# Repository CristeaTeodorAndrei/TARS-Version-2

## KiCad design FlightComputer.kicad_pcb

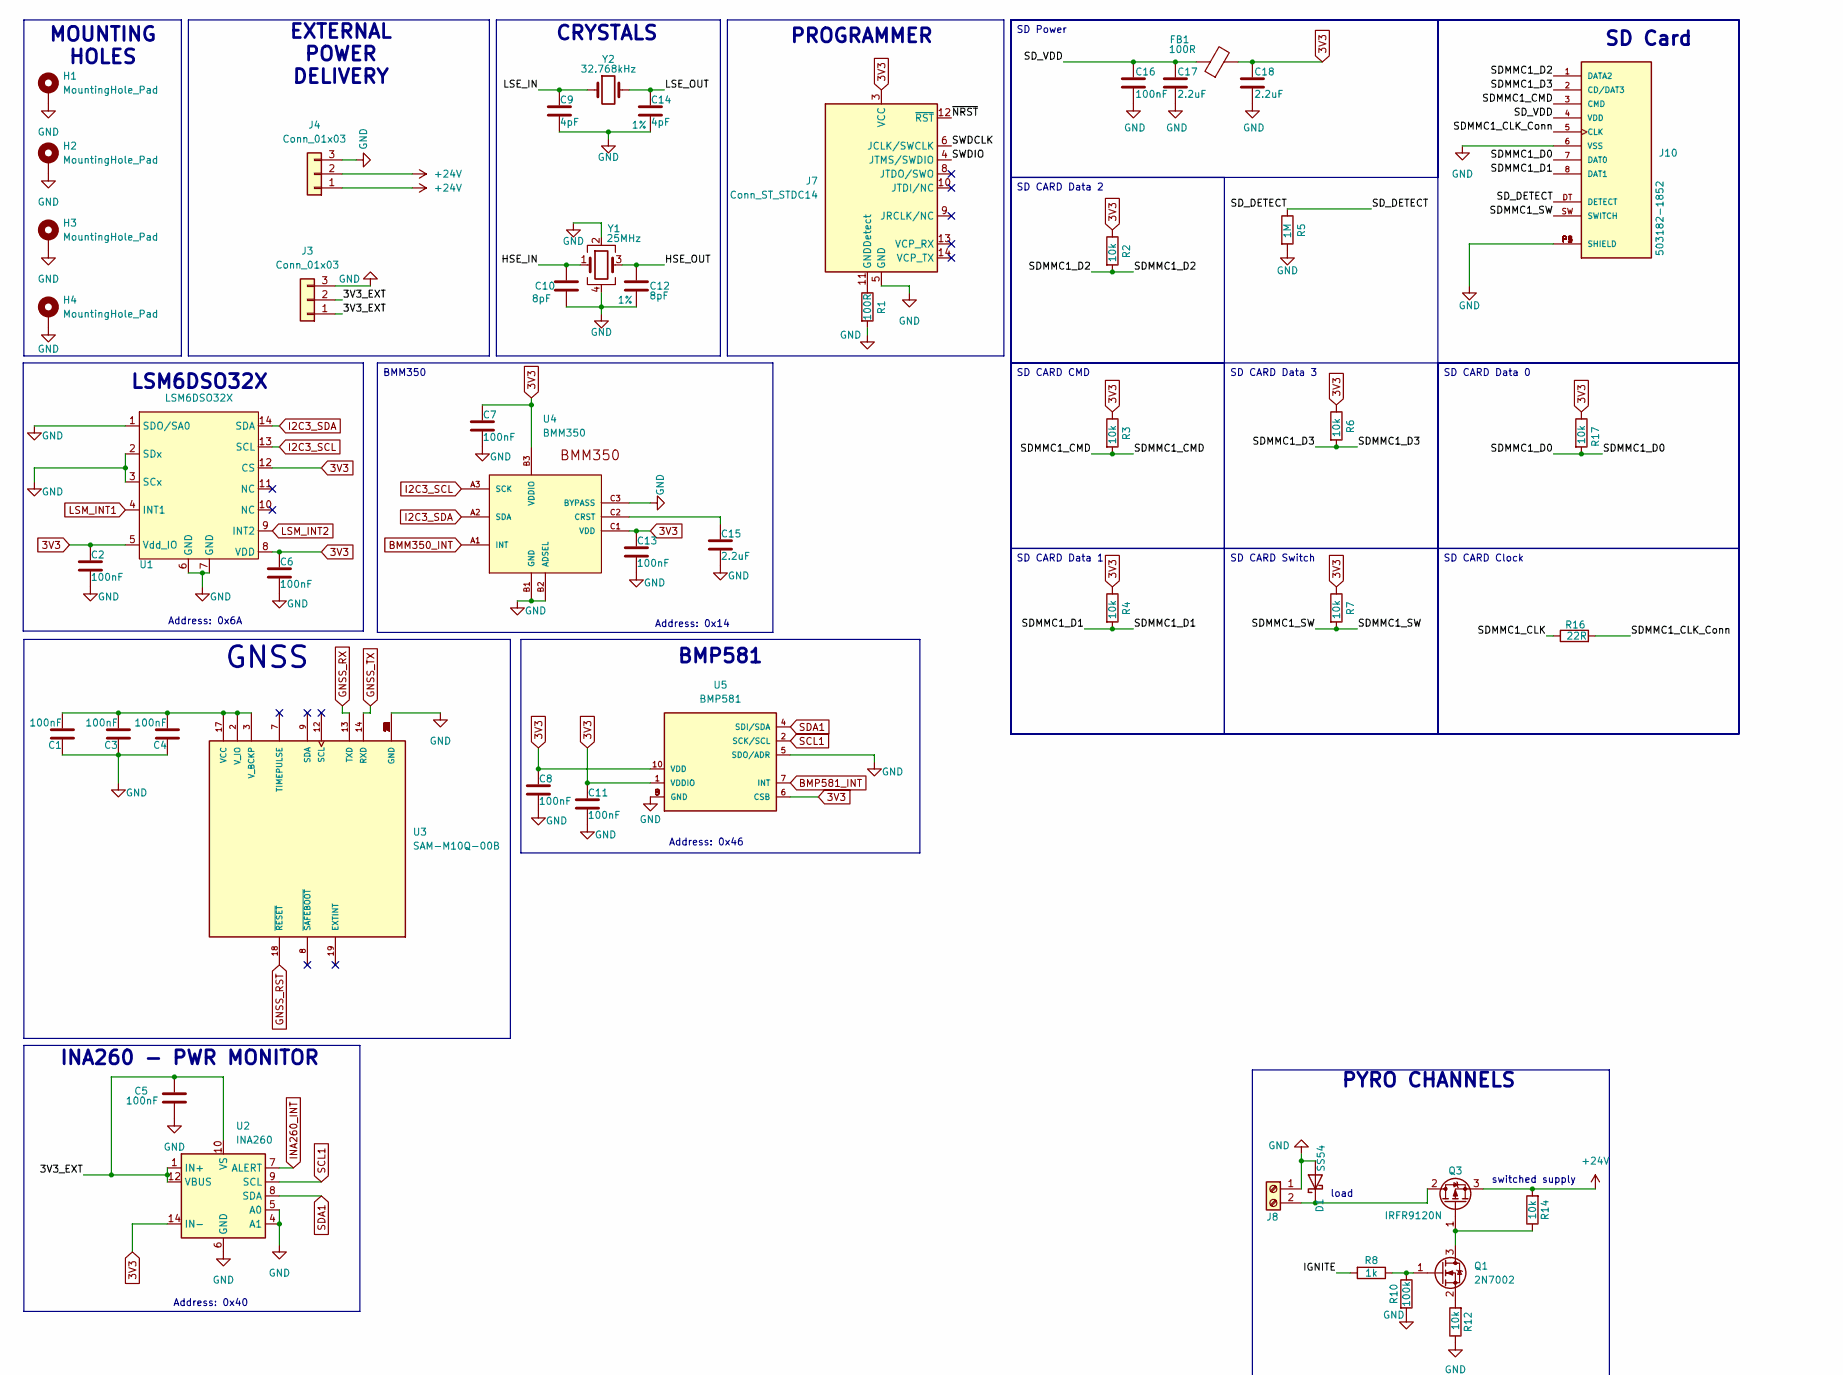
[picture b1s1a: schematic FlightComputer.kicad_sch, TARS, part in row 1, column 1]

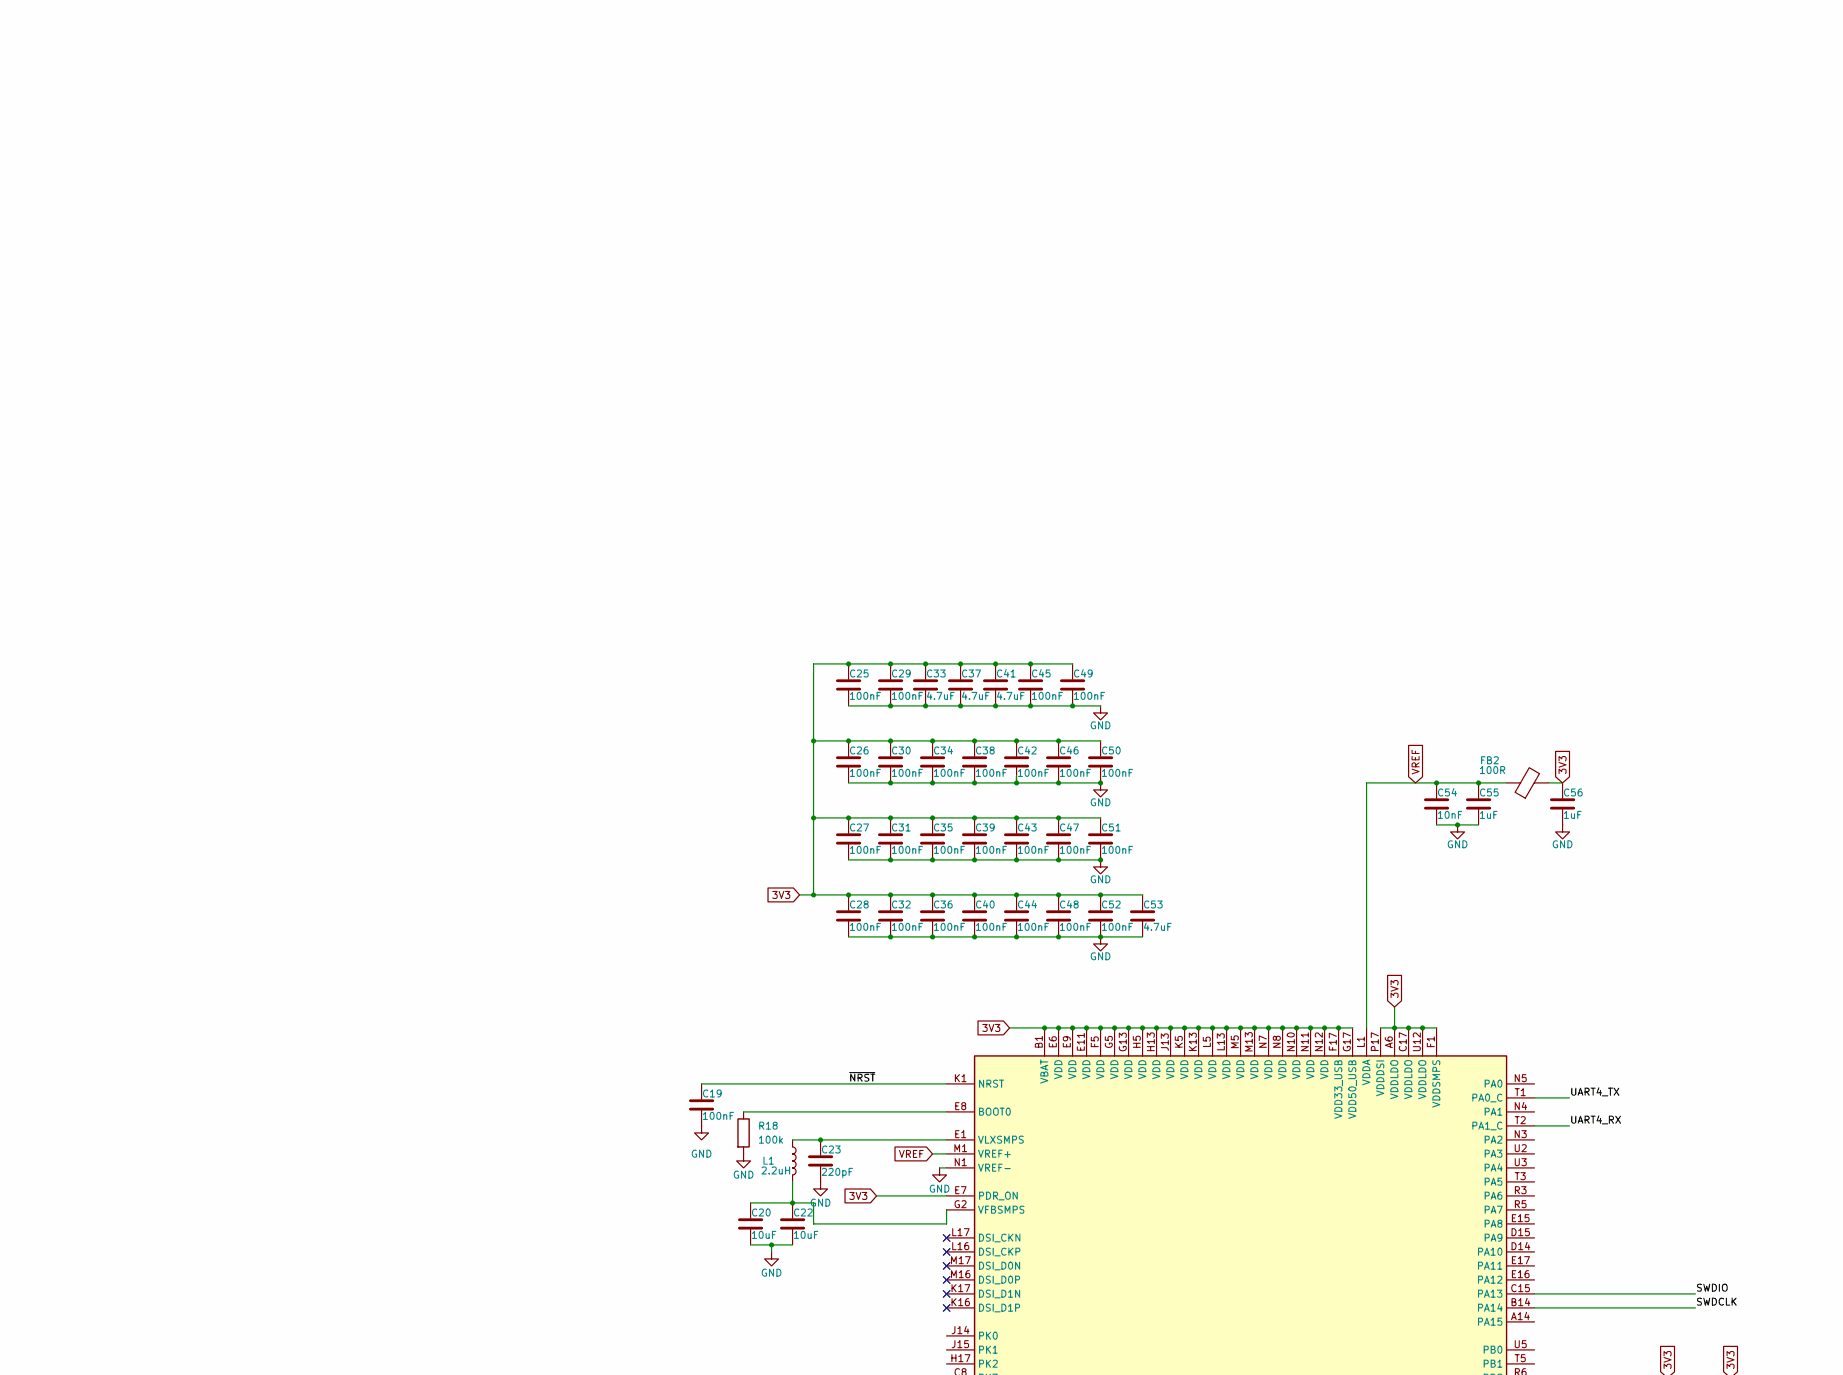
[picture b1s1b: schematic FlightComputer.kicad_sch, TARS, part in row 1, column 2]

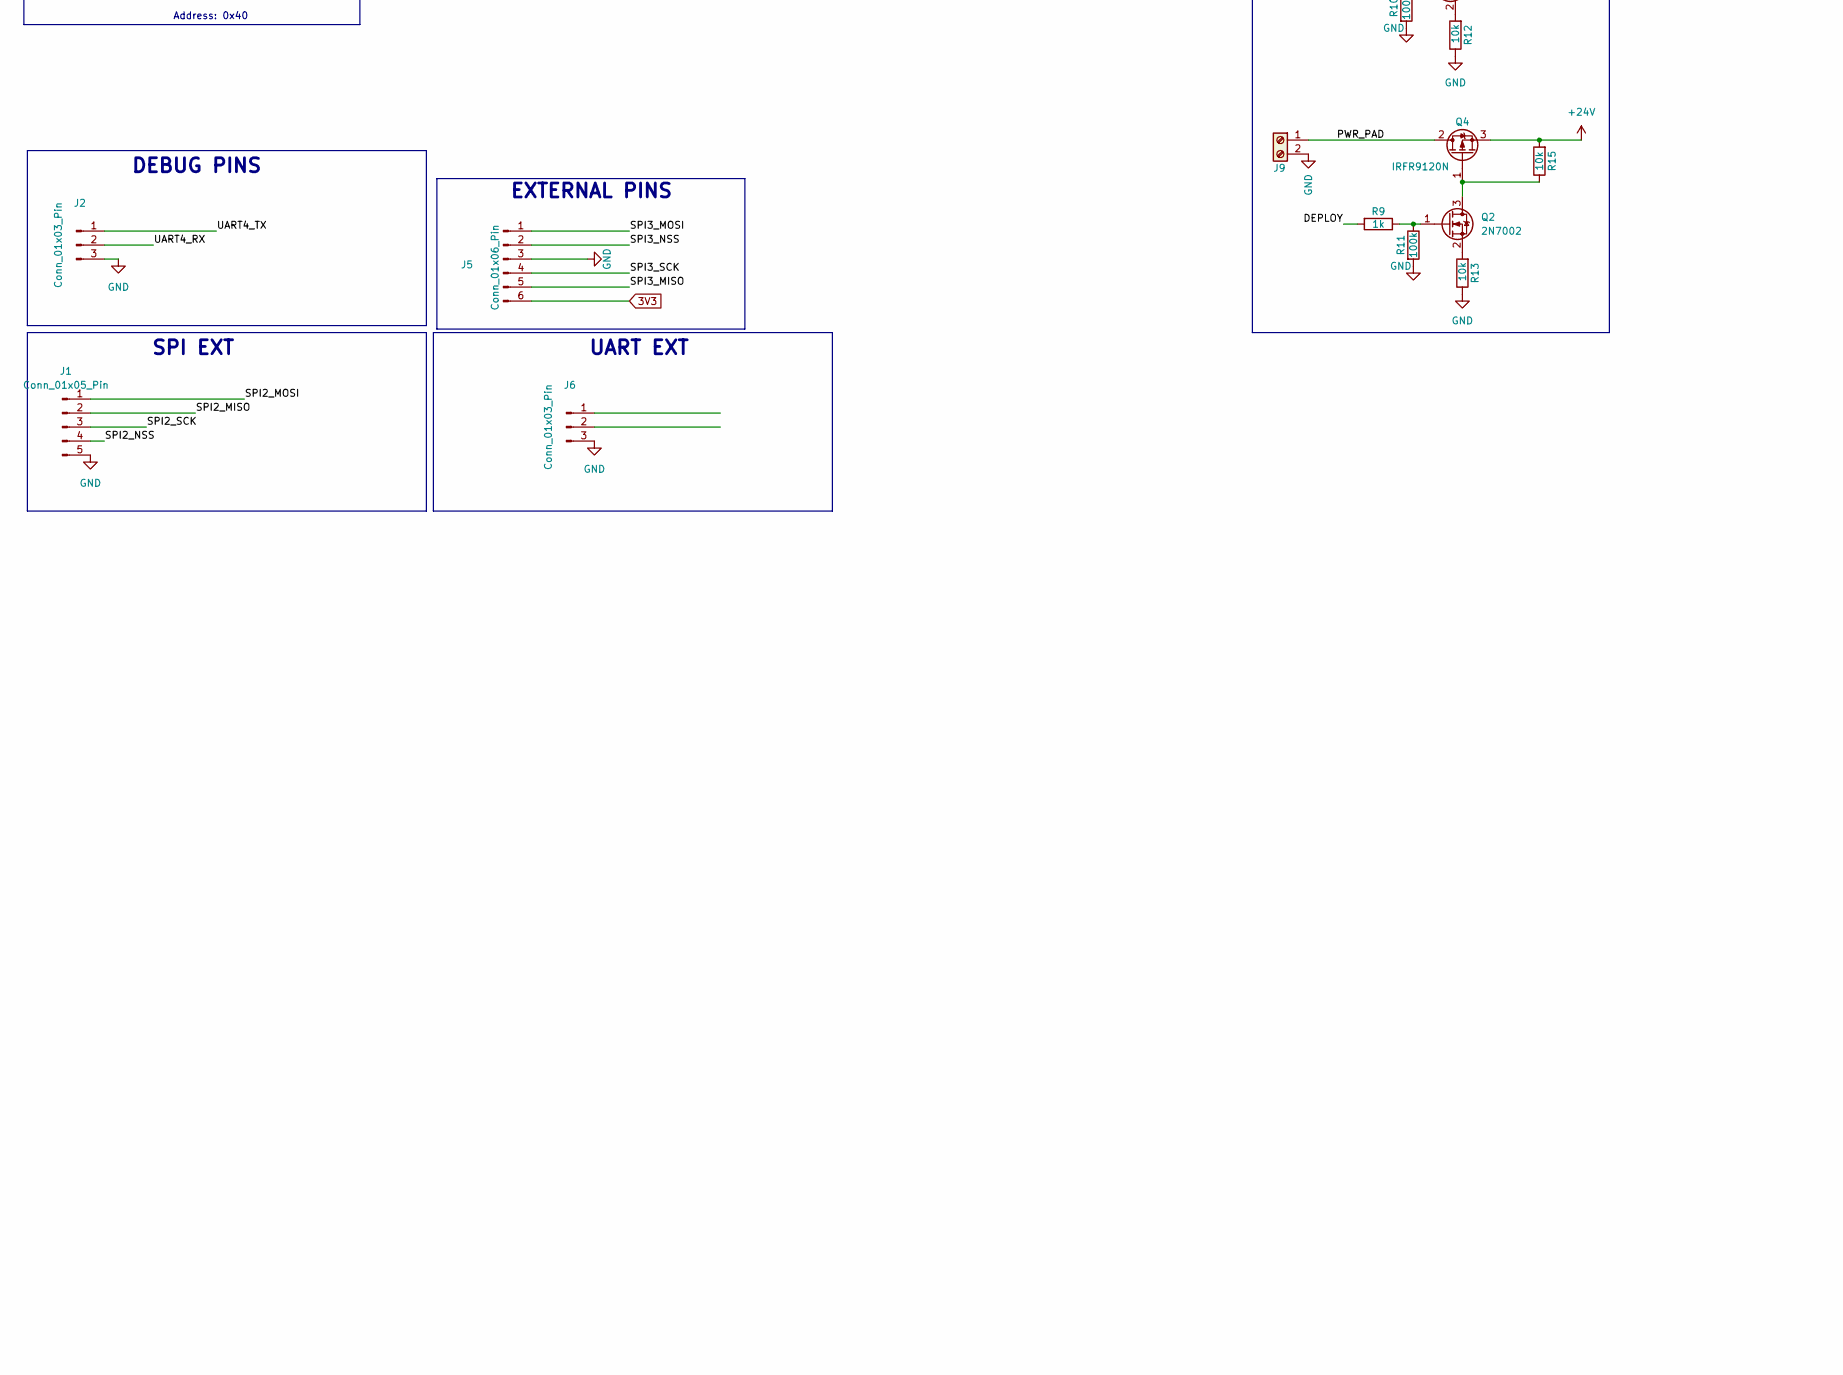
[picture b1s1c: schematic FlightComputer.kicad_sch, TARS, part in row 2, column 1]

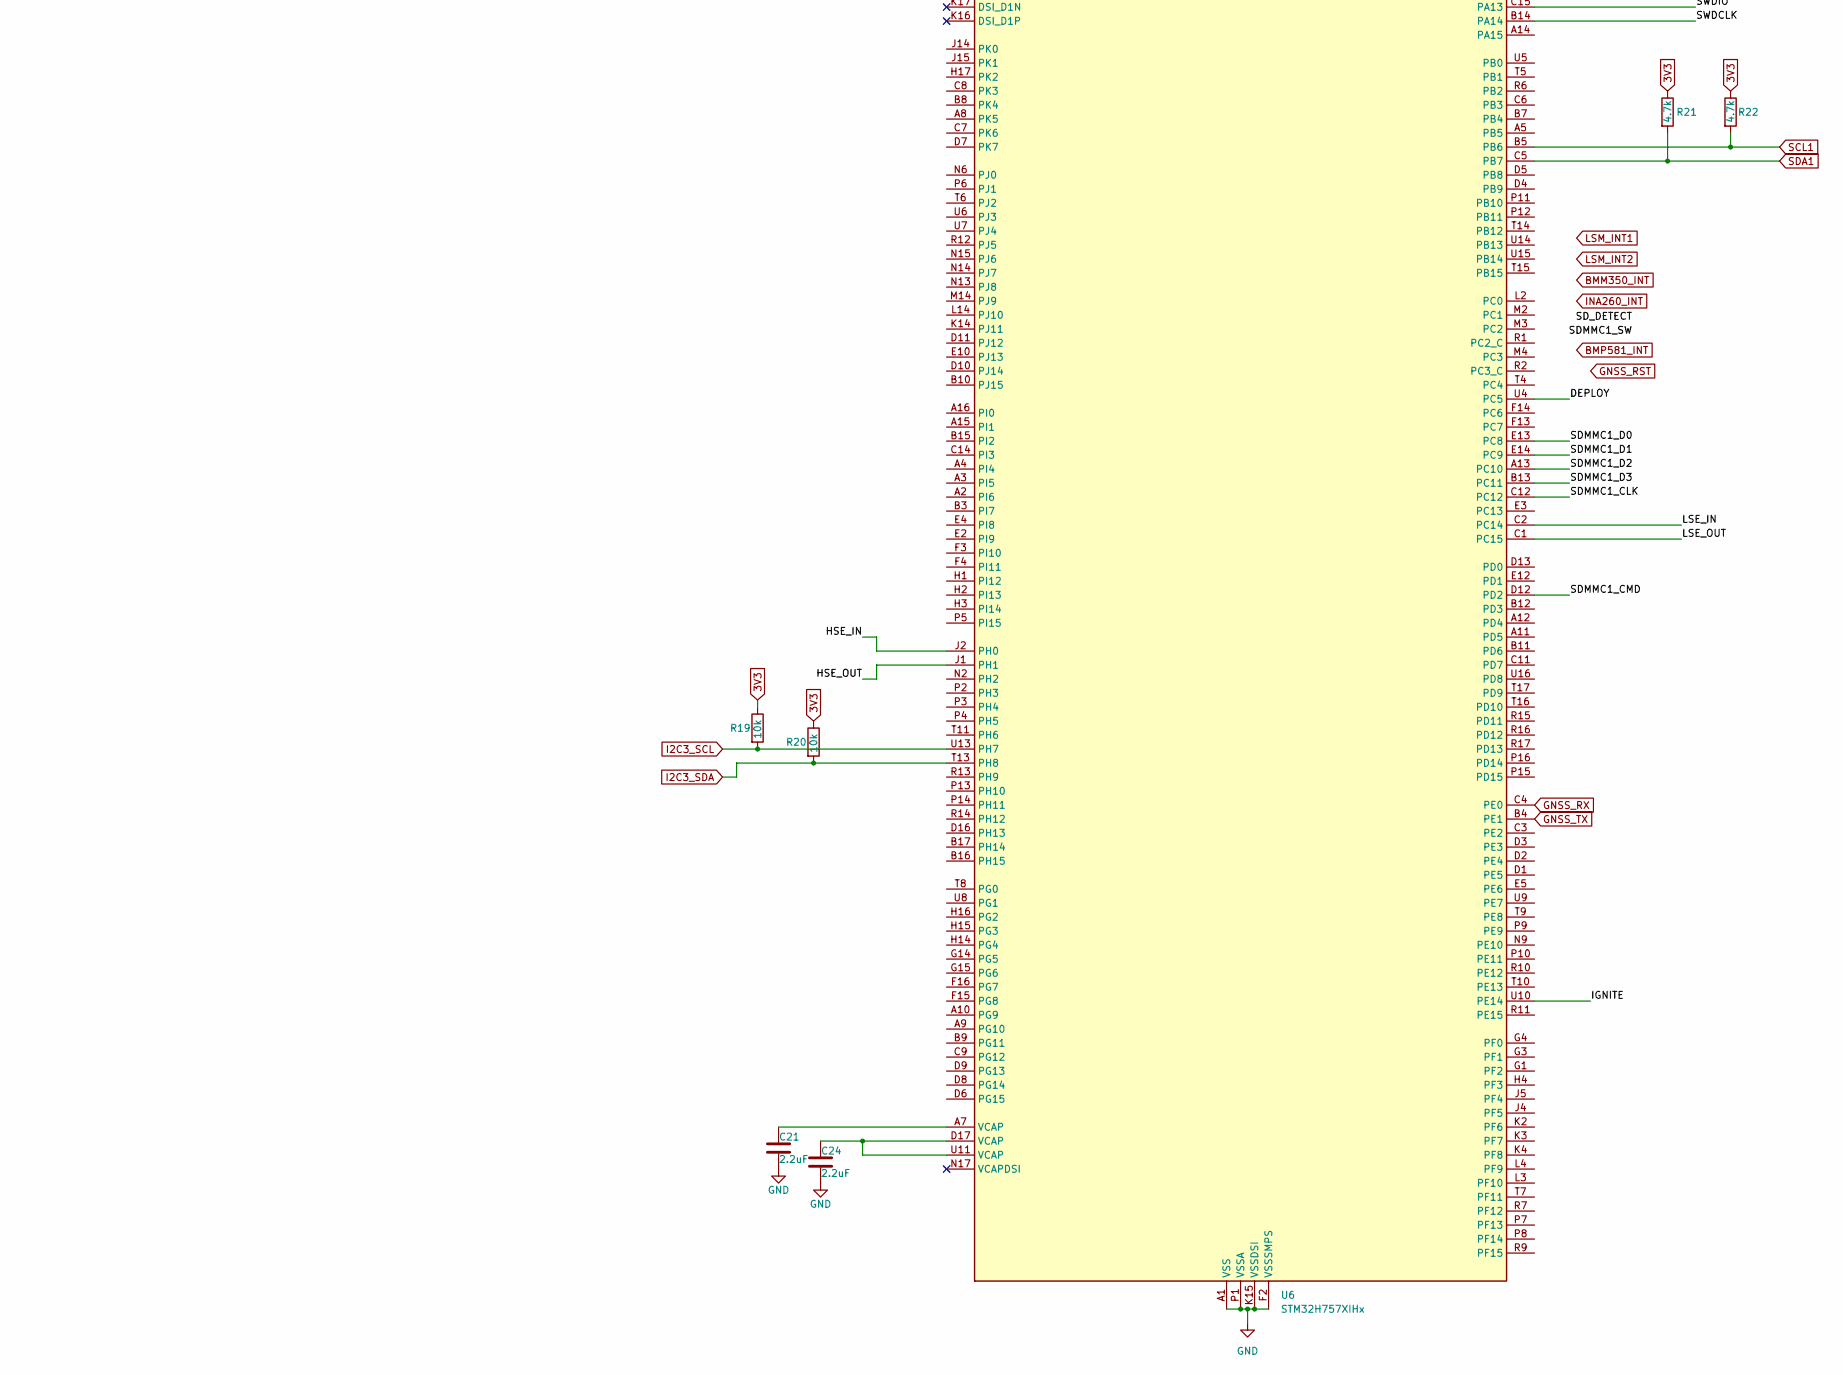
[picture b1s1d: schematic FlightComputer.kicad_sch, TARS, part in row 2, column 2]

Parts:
C1, C3, C19, C27, C28, C31, C32, C35, C36, C39, C40, C43, C44, C47, C48, C51, C52: 100nF; C_0402_1005Metric
C2, C4, C6, C7, C8, C11, C13, C25, C26, C29, C30, C34, C38, C42, C45, C46, C49, C50: 100nF; C_0603_1608Metric
C5: 100nF; C_0805_2012Metric
C9: 4pF; C_0402_1005Metric; JLCPCB C1568
C10: 8pF; C_0402_1005Metric
C12: 8pF; C_0402_1005Metric; Tolerance 1%
C14: 4pF; C_0402_1005Metric; Tolerance 1%; JLCPCB C1568
C15, C21, C24: 2.2uF; C_0402_1005Metric
C16: 100nF; C_0603_1608Metric; JLCPCB C285034
C17, C18: 2.2uF; C_0603_1608Metric; JLCPCB C23630
C20, C22: 10uF; C_0402_1005Metric
C23: 220pF; C_0402_1005Metric
C33, C37, C41: 4.7uF; C_0603_1608Metric
C53: 4.7uF; C_0402_1005Metric
C54: 10nF; C_0603_1608Metric; JLCPCB C15195
C55, C56: 1uF; C_0603_1608Metric; JLCPCB C52923
D1: SS54; D_SMA
FB1, FB2: 100R; L_0603_1608Metric
H1, H2, H3, H4: MountingHole_Pad; MountingHole_2.7mm_M2.5_Pad_Via
J1: Conn_01x05_Pin; JST_PH_S5B-PH-SM4-TB_1x05-1MP_P2.00mm_Horizontal; JLCPCB C265104
J2: Conn_01x03_Pin; JST_PH_S3B-PH-SM4-TB_1x03-1MP_P2.00mm_Horizontal
J3, J4: Conn_01x03; JST_PH_S3B-PH-SM4-TB_1x03-1MP_P2.00mm_Horizontal; JLCPCB C265101
J5: Conn_01x06_Pin; JST_PH_S8B-PH-SM4-TB_1x08-1MP_P2.00mm_Horizontal; JLCPCB C265405
J6: Conn_01x03_Pin; JST_PH_S3B-PH-SM4-TB_1x03-1MP_P2.00mm_Horizontal; JLCPCB C265101
J7: Conn_ST_STDC14; PinHeader_2x07_P1.27mm_Vertical_SMD
J8, J9: Screw_Terminal_01x02; WAGO_2060-452_998-404; JLCPCB C2765055
J10: 503182-1852; MOLEX_503182-1852; JLCPCB C587953
L1: 2.2uH; C_1812_4532Metric; JLCPCB C86093
Q1, Q2: 2N7002; SOT-23
Q3, Q4: IRFR9120N; TO229P990X239-3N
R1: 100R; R_0402_1005Metric; JLCPCB C25900
R2, R3, R4, R6, R7, R17: 10k; R_0402_1005Metric
R5: 1M; R_0402_1005Metric; JLCPCB C409676
R8, R9: 1k; R_0402_1005Metric; JLCPCB C11702
R10, R11: 100k; R_0402_1005Metric
R12, R13, R14, R15, R19, R20: 10k; R_0603_1608Metric
R16: 22R; R_0402_1005Metric; JLCPCB C25092
R18: 100k; R_0603_1608Metric
R21, R22: 4.7k; R_0603_1608Metric
U1: LGA-14_3x2.5mm_P0.5mm_LayoutBorder3x4y; JLCPCB C3663738
U2: INA260; TSSOP-16_4.4x5mm_P0.65mm; JLCPCB C2155885
U3: SAM-M10Q-00B; XCVR_SAM-M10Q-00B; PARTREV R03
U4: BMM350; BGA9C40P3X3_128X128X50; JLCPCB C17225907
U5: BMP581; JLCPCB C22391138
U6: STM32H757XIHx; TFBGA-265_14x14mm_Layout17x17_P0.8mm
Y1: 25MHz; Crystal_SMD_3225-4Pin_3.2x2.5mm; JLCPCB C479202
Y2: 32.768kHz; Crystal_SMD_2012-2Pin_2.0x1.2mm; JLCPCB C99009

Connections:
3V3: C2.1, C6.1, C7.1, C8.1, C11.1, C13.1, C18.1, C25.1, C26.1, C27.1, C28.1, C29.1, C30.1, C31.1, C32.1, C33.1, C34.1, C35.1, C36.1, C37.1, C38.1, C39.1, C40.1, C41.1, C42.1, C43.1, C44.1, C45.1, C46.1, C47.1, C48.1, C49.1, C50.1, C51.1, C52.1, C53.1, C56.1, FB1.2, FB2.2, J5.6, J7.3 (VCC), R2.1, R3.1, R4.1, R6.1, R7.1, R17.1, R19.1, R20.1, R21.1, R22.1, U1.5 (Vdd_IO), U1.8 (VDD), U1.12 (CS), U2.14 (IN-), U2.15 (IN-), U2.16 (IN-), U4.B3 (VDDIO), U4.C1 (VDD), U5.1 (VDDIO), U5.6 (CSB), U5.10 (VDD), U6.A6 (VDDLDO), U6.B1 (VBAT), U6.C17 (VDDLDO), U6.E6 (VDD), U6.E7 (PDR_ON), U6.E9 (VDD), U6.E11 (VDD), U6.F1 (VDDSMPS), U6.F5 (VDD), U6.F17 (VDD33_USB), U6.G5 (VDD), U6.G13 (VDD), U6.G17 (VDD50_USB), U6.H5 (VDD), U6.H13 (VDD), U6.J13 (VDD), U6.K5 (VDD), U6.K13 (VDD), U6.L5 (VDD), U6.L13 (VDD), U6.M5 (VDD), U6.M13 (VDD), U6.N7 (VDD), U6.N8 (VDD), U6.N10 (VDD), U6.N11 (VDD), U6.N12 (VDD), U6.P17 (VDDDSI), U6.U12 (VDDLDO); also elsewhere on the board
+24V: J4.1, J4.2, Q3.3 (S), Q4.3 (S), R14.2, R15.2
/3V3_EXT: C5.1, J3.1, J3.2, U2.1 (IN+), U2.2 (IN+), U2.3 (IN+), U2.10 (VS), U2.12 (VBUS)
/DEPLOY: R9.2, U6.U4 (PC5)
/HSE_IN: C10.1, U6.J2 (PH0), Y1.1
/HSE_OUT: C12.1, U6.J1 (PH1), Y1.3
/IGNITE: R8.2, U6.U10 (PE14)
/LSE_IN: C9.1, U6.C2 (PC14), Y2.1
/LSE_OUT: C14.1, U6.C1 (PC15), Y2.2
/PWR_PAD: J9.1, Q4.2 (D)
/SDMMC1_CLK: R16.1, U6.C12
/SDMMC1_CLK_Conn: J10.5 (CLK), R16.2
/SDMMC1_CMD: J10.3 (CMD), R3.2, U6.D12 (PD2)
/SDMMC1_D0: J10.7 (DAT0), R17.2, U6.E13 (PC8)
/SDMMC1_D1: J10.8 (DAT1), R4.2, U6.E14 (PC9)
/SDMMC1_D2: J10.1 (DATA2), R2.2, U6.A13 (PC10)
/SDMMC1_D3: J10.2 (CD/DAT3), R6.2, U6.B13 (PC11)
/SDMMC1_SW: J10.SW (SWITCH), R7.2
/SD_DETECT: J10.DT (DETECT), R5.1
/SD_VDD: C16.1, C17.1, FB1.1, J10.4 (VDD)
/SPI2_MISO: J1.2
/SPI2_MOSI: J1.1
/SPI2_NSS: J1.4
/SPI2_SCK: J1.3
/SPI3_MISO: J5.5
/SPI3_MOSI: J5.1
/SPI3_NSS: J5.2
/SPI3_SCK: J5.4
/SWDCLK: J7.6 (JCLK/SWCLK), U6.B14 (PA14)
/SWDIO: J7.4 (JTMS/SWDIO), U6.C15 (PA13)
/UART4_RX: J2.2, U6.T2 (PA1_C)
/UART4_TX: J2.1, U6.T1 (PA0_C)
/~NRST: C19.1, J7.12 (~RST), U6.K1 (NRST)
BMM350_INT: U4.A1 (INT)
BMP581_INT: U5.7 (INT)
GND: C1.1, C2.2, C3.1, C4.1, C5.2, C6.2, C7.2, C8.2, C9.2, C10.2, C11.2, C12.2, C13.2, C14.2, C15.2, C16.2, C17.2, C18.2, C19.2, C20.2, C21.2, C22.2, C23.2, C24.2, C25.2, C26.2, C27.2, C28.2, C29.2, C30.2, C31.2, C32.2, C33.2, C34.2, C35.2, C36.2, C37.2, C38.2, C39.2, C40.2, C41.2, C42.2, C43.2, C44.2, C45.2, C46.2, C47.2, C48.2, C49.2, C50.2, C51.2, C52.2, C53.2, C54.2, C55.2, C56.2, D1.2 (A), H1.1, H2.1, H3.1, H4.1, J1.5, J2.3, J3.3, J4.3, J5.3, J6.3, J7.5 (GND), J7.7 (GND), J8.1, J9.2, J10.6 (VSS), J10.P1 (SHIELD), J10.P2 (SHIELD), J10.P3 (SHIELD), J10.P4 (SHIELD), J10.P5 (SHIELD), R1.2, R5.2, R10.2, R11.2, R12.1, R13.1, R18.2, U1.1 (SDO/SA0), U1.2 (SDx), U1.3 (SCx), U1.6 (GND), U1.7 (GND), U2.4 (A1), U2.5 (A0), U2.6 (GND), U2.11 (GND), U3.1 (GND), U3.4 (GND), U3.5 (GND), U3.6 (GND), U3.10 (GND), U3.11 (GND), U3.15 (GND), U3.16 (GND), U3.20 (GND), U4.B1 (GND), U4.B2 (ADSEL), U4.C3 (BYPASS), U5.3 (GND), U5.5 (SDO/ADR), U5.8 (GND), U5.9 (GND), U6.A1 (VSS), U6.A17 (VSS), U6.B2 (VSS), U6.B6 (VSS), U6.C10 (VSS), U6.C13 (VSS), U6.C16 (VSS), U6.F2 (VSSSMPS), U6.G7 (VSS), U6.G8 (VSS), U6.G9 (VSS), U6.G10 (VSS), U6.G11 (VSS), U6.G16 (VSS), U6.H7 (VSS), U6.H8 (VSS), U6.H9 (VSS), U6.H10 (VSS), U6.H11 (VSS), U6.J3 (VSS), U6.J7 (VSS), U6.J8 (VSS), U6.J9 (VSS), U6.J10 (VSS), U6.J11 (VSS), U6.J16 (VSS), U6.J17 (VSS), U6.K7 (VSS), U6.K8 (VSS), U6.K9 (VSS), U6.K10 (VSS), U6.K11 (VSS), U6.K15 (VSSDSI), U6.L7 (VSS), U6.L8 (VSS), U6.L9 (VSS), U6.L10 (VSS), U6.L11 (VSS), U6.L15 (VSSDSI), U6.M15 (VSSDSI), U6.N1 (VREF-), U6.N16 (VSS), U6.P1 (VSSA), U6.R4 (VSS), U6.R8 (VSS), U6.T12 (VSS), U6.U1 (VSS), U6.U17 (VSS), Y1.2, Y1.4
GNSS_RST: U3.18 (~RESET)
GNSS_RX: U3.13 (TXD), U6.C4 (PE0)
GNSS_TX: U3.14 (RXD), U6.B4 (PE1)
I2C3_SCL: R19.2, U1.13 (SCL), U4.A3 (SCK), U6.U13 (PH7)
I2C3_SDA: R20.2, U1.14 (SDA), U4.A2 (SDA), U6.T13 (PH8)
INA260_INT: U2.7 (ALERT)
LSM_INT1: U1.4 (INT1)
LSM_INT2: U1.9 (INT2)
unnamed: C21.1, U6.A7 (VCAP)
unnamed: C24.1, U6.D17 (VCAP), U6.U11 (VCAP)
unnamed: D1.1 (K), J8.2, Q3.2 (D)
unnamed: J7.11 (GNDDetect), R1.1
unnamed: Q1.3 (D), Q3.1 (G), R14.1
unnamed: Q1.1 (G), R8.1, R10.1
unnamed: Q1.2 (S), R12.2
unnamed: Q2.3 (D), Q4.1 (G), R15.1
unnamed: Q2.1 (G), R9.1, R11.1
unnamed: Q2.2 (S), R13.2
unnamed: C1.2, C3.2, C4.2, U3.2 (V_IO), U3.3 (V_BCKP), U3.17 (VCC)
unnamed: C15.1, U4.C2 (CRST)
unnamed: R18.1, U6.E8 (BOOT0)
unnamed: C20.1, C22.1, L1.2, U6.G2 (VFBSMPS)
unnamed: C23.1, L1.1, U6.E1 (VLXSMPS)
SCL1: R22.2, U2.9 (SCL), U5.2 (SCK/SCL), U6.B5 (PB6)
SDA1: R21.2, U2.8 (SDA), U5.4 (SDI/SDA), U6.C5 (PB7)
VREF: C54.1, C55.1, FB2.1, U6.L1 (VDDA), U6.M1 (VREF+)

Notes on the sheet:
PYRO CHANNELS
Address: 0x46
Address: 0x40
INA260 - PWR MONITOR
SD Card
MOUNTING HOLES
SPI EXT
Address: 0x6A
EXTERNAL PINS
EXTERNAL POWER DELIVERY
Address: 0x14
LSM6DSO32X
PROGRAMMER
CRYSTALS
DEBUG PINS
UART EXT
load
switched supply
BMP581
SD CARD CMD
GNSS
SD CARD Data 3
SD CARD Data 1
SD Power
BMM350
SD CARD Data 0
SD CARD Switch
SD CARD Data 2
SD CARD Clock

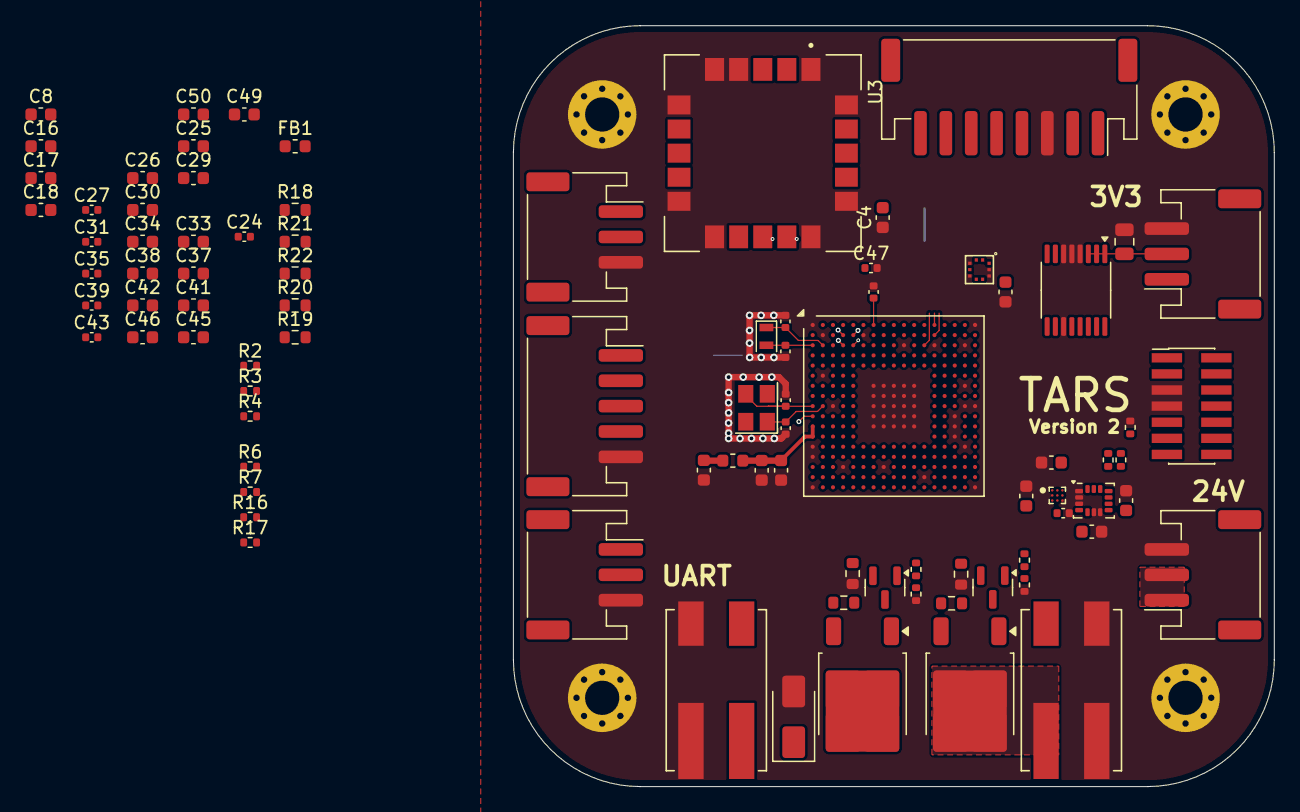
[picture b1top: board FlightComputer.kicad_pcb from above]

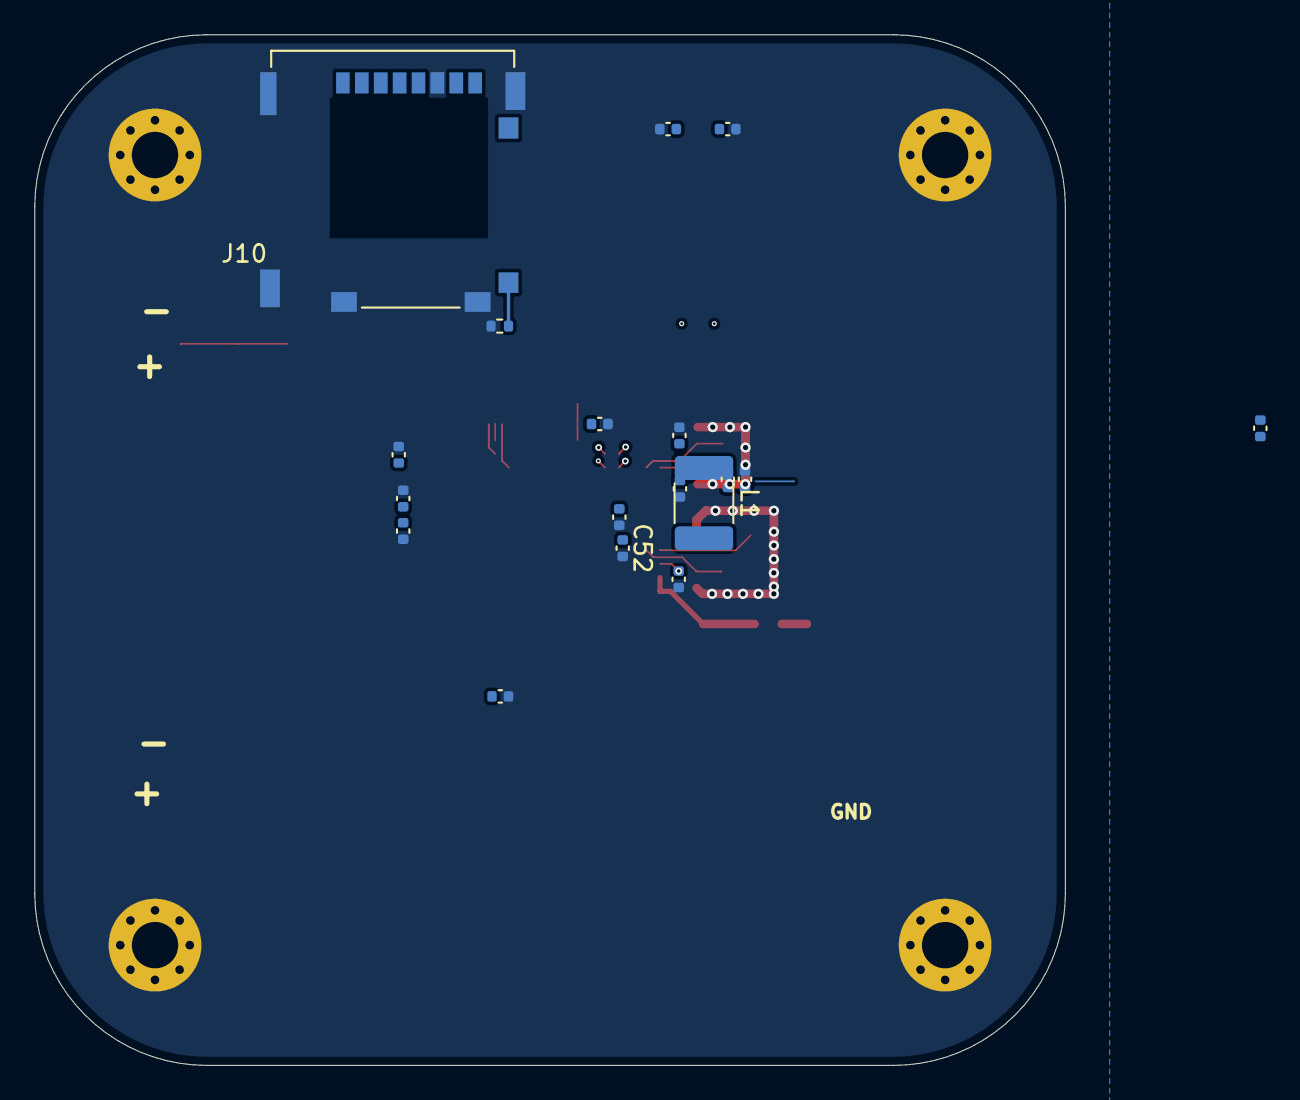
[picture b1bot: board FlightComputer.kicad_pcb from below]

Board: 6 copper layers, 60.0 x 60.0 mm, 110 parts (18 on the bottom side), 48 nets.

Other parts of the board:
R10#2, R11#2: 10k; R_0402_1005Metric

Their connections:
3V3: R10#2.1, R11#2.2; also elsewhere on the board

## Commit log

2025-06-24 added the files
2025-06-24 Added GPS
2025-06-27 added files for the schematic
